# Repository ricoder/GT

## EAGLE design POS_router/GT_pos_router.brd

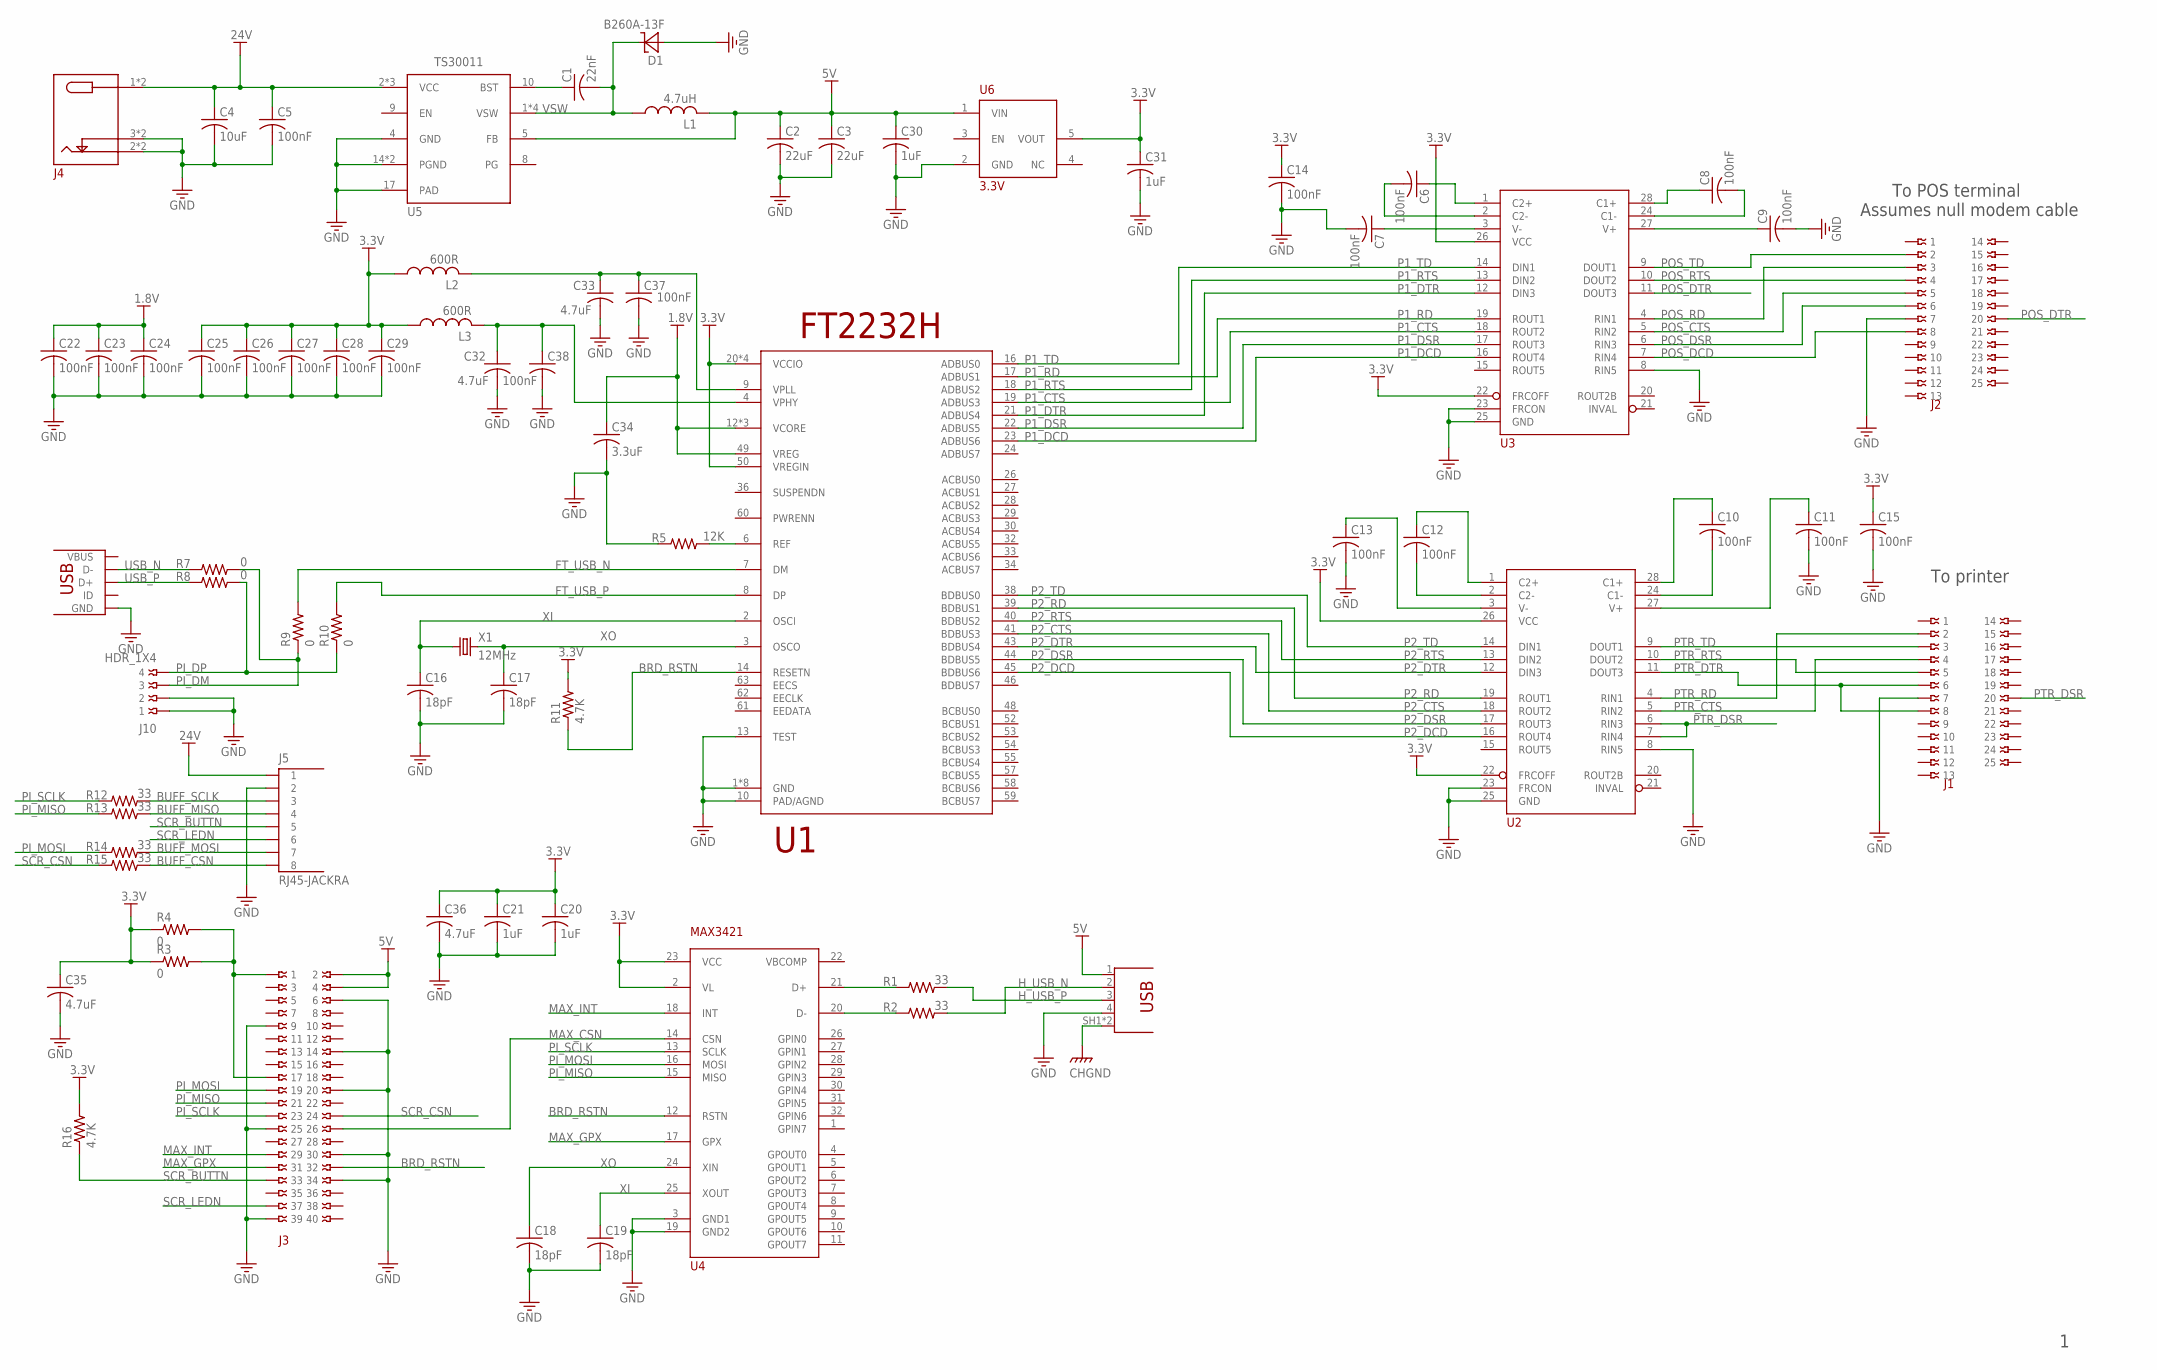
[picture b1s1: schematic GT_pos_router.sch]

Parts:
C1: 22nF; CAPC100X50X55L25N
C2, C3: 22uF; CAPC3216X85L50N
C4: 10uF; CAPC3216X85L50N
C5, C6, C7, C8, C9, C10, C11, C12, C13, C14, C15: 100nF; CAPC1608X87L35N
C16, C17, C18, C19: 18pF; CAPC100X50X55L25N
C20, C21, C30, C31: 1uF; CAPC1608X87L35N
C22, C23, C24, C25, C26, C27, C28, C29, C37, C38: 100nF; CAPC100X50X55L25N
C32, C33, C35, C36: 4.7uF; CAPC2012X140L50N
C34: 3.3uF; CAPC1608X87L35N
D1: B260A-13F; SODFL430X260X240L114X145N
J1: DB25-RA-MALE
J2: DB25-RA-FEMALE
J3: RPI_ZERO_HDR0.2_STACK; RPI_ZERO_HDR
J4: PWR_JACK_SW_NC; PJ-202B
J5: RJ45-JACKRA; RJ45-RA
J8: USB-MICRO-B-SMT-FLG; 10118192-0001LF
J9: USB-A-RECEPT-RA; SS-52100-001
J10: HDR_1X4; HDR_0.1IN_1X4_1MM
L1: 4.7uH; SRN4026
L2, L3: 600R; INDC100X50X55L25N
R1, R2, R12, R13, R14, R15: 33; RESC1005X40L25N
R3, R4, R7, R8, R9, R10: 0; RESC1005X40L25N
R5: 12K; RESC1005X40L25N
R11, R16: 4.7K; RESC1005X40L25N
U1: FT2232H; LQFP64P050_120X120X160N
U2, U3: MAX3243ST-EB; TSSOP28
U4: MAX3421; TQFP32P050_50X50X120N
U5: TS30011; QFN16P05_3X3X10T17X17N
U6: 3.3V; SOT23-5P95_280X160L40X40N
X1: 12MHz; ABLS2

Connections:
1.8V: C22.1, C23.1, C24.1, C34.1, U1.12 (VCORE), U1.37 (VCORE), U1.49 (VREG), U1.64 (VCORE)
3.3V: C14.1, C15.1, C20.1, C21.1, C25.1, C26.1, C27.1, C28.1, C29.1, C31.1, C35.1, C36.1, L2.1, L3.1, R3.1, R4.1, R11.2, R16.2, U1.20 (VCCIO), U1.31 (VCCIO), U1.42 (VCCIO), U1.50 (VREGIN), U1.56 (VCCIO), U2.22 (FRCOFF), U2.26 (VCC), U3.22 (FRCOFF), U3.26 (VCC), U4.2 (VL), U4.23 (VCC), U6.5 (VOUT)
5V: C2.1, C3.1, C30.1, J3.2, J3.4, J9.1 (VBUS), L1.2, U5.5 (FB), U6.1 (VIN)
24V: C4.1, C5.1, J4.1, J4.4 (1), J5.1, U5.2 (VCC), U5.3 (VCC), U5.11 (VCC)
BRD_RSTN: J3.32, R11.1, U1.14 (RESETN), U4.12 (RSTN)
BUFF_CSN: J5.8, R15.2
BUFF_MISO: J5.4, R13.2
BUFF_MOSI: J5.7, R14.2
BUFF_SCLK: J5.3, R12.2
CHGND: J9.SH1 (SHELL), J9.SH2 (SHELL)
FT_USB_N: R9.2, U1.7 (DM)
FT_USB_P: R10.2, U1.8 (DP)
GND: C2.2, C3.2, C4.2, C5.2, C7.2, C9.2, C11.2, C13.2, C14.2, C15.2, C16.2, C17.2, C18.2, C19.2, C20.2, C21.2, C22.2, C23.2, C24.2, C25.2, C26.2, C27.2, C28.2, C29.2, C30.2, C31.2, C32.2, C33.2, C34.2, C35.2, C36.2, C37.2, C38.2, D1.A, J1.7, J2.7, J3.6, J3.9, J3.14, J3.20, J3.25, J3.30, J3.34, J3.39, J4.2, J4.3, J4.5 (2), J4.6 (3), J5.2, J8.5 (GND), J9.4 (GND), J10.1, J10.2, R5.1, U1.1 (GND), U1.5 (GND), U1.10 (PAD/AGND), U1.11 (GND), U1.13 (TEST), U1.15 (GND), U1.25 (GND), U1.35 (GND), U1.47 (GND), U1.51 (GND), U2.8 (RIN5), U2.23 (FRCON), U2.25 (GND), U3.8 (RIN5), U3.23 (FRCON), U3.25 (GND), U4.3 (GND1), U4.19 (GND2), U5.4 (GND), U5.14 (PGND), U5.15 (PGND), U5.17 (PAD), U6.2 (GND)
H_USB_N: J9.2 (D-), R2.2
H_USB_P: J9.3 (D+), R1.2
MAX_CSN: J3.26, U4.14 (CSN)
MAX_GPX: J3.31, U4.17 (GPX)
MAX_INT: J3.29, U4.18 (INT)
unnamed: R1.1, U4.21 (D+)
unnamed: R2.1, U4.20 (D-)
unnamed: C1.1, U5.10 (BST)
unnamed: C6.1, U3.1 (C2+)
unnamed: C6.2, U3.2 (C2-)
unnamed: C7.1, U3.3 (V-)
unnamed: C33.1, C37.1, L2.2, U1.9 (VPLL)
unnamed: C8.1, U3.28 (C1+)
unnamed: C8.2, U3.24 (C1-)
unnamed: C9.1, U3.27 (V+)
unnamed: C32.1, C38.1, L3.2, U1.4 (VPHY)
unnamed: R5.2, U1.6 (REF)
unnamed: C13.1, U2.3 (V-)
unnamed: C12.2, U2.2 (C2-)
unnamed: C12.1, U2.1 (C2+)
unnamed: C10.1, U2.28 (C1+)
unnamed: C10.2, U2.24 (C1-)
unnamed: C11.1, U2.27 (V+)
unnamed: J3.1, J3.17, R3.2, R4.2
P1_CTS: U1.19 (ADBUS3), U3.18 (ROUT2)
P1_DCD: U1.23 (ADBUS6), U3.16 (ROUT4)
P1_DSR: U1.22 (ADBUS5), U3.17 (ROUT3)
P1_DTR: U1.21 (ADBUS4), U3.12 (DIN3)
P1_RD: U1.17 (ADBUS1), U3.19 (ROUT1)
P1_RTS: U1.18 (ADBUS2), U3.13 (DIN2)
P1_TD: U1.16 (ADBUS0), U3.14 (DIN1)
P2_CTS: U1.41 (BDBUS3), U2.18 (ROUT2)
P2_DCD: U1.45 (BDBUS6), U2.16 (ROUT4)
P2_DSR: U1.44 (BDBUS5), U2.17 (ROUT3)
P2_DTR: U1.43 (BDBUS4), U2.12 (DIN3)
P2_RD: U1.39 (BDBUS1), U2.19 (ROUT1)
P2_RTS: U1.40 (BDBUS2), U2.13 (DIN2)
P2_TD: U1.38 (BDBUS0), U2.14 (DIN1)
PI_DM: J10.3, R7.2, R9.1
PI_DP: J10.4, R8.2, R10.1
PI_MISO: J3.21, R13.1, U4.15 (MISO)
PI_MOSI: J3.19, R14.1, U4.16 (MOSI)
PI_SCLK: J3.23, R12.1, U4.13 (SCLK)
POS_CTS: J2.5, U3.5 (RIN2)
POS_DCD: J2.8, U3.7 (RIN4)
POS_DSR: J2.6, U3.6 (RIN3)
POS_DTR: J2.20, U3.11 (DOUT3)
POS_RD: J2.3, U3.4 (RIN1)
POS_RTS: J2.4, U3.10 (DOUT2)
POS_TD: J2.2, U3.9 (DOUT1)
PTR_CTS: J1.4, U2.5 (RIN2)
PTR_DSR: J1.20, U2.6 (RIN3), U2.7 (RIN4)
PTR_DTR: J1.6, J1.8, U2.11 (DOUT3)
PTR_RD: J1.2, U2.4 (RIN1)
PTR_RTS: J1.5, U2.10 (DOUT2)
PTR_TD: J1.3, U2.9 (DOUT1)
SCR_BUTTN: J3.33, J5.5, R16.1
SCR_CSN: J3.24, R15.1
SCR_LEDN: J3.37, J5.6
USB_N: J8.2 (D-), R7.1
USB_P: J8.3 (D+), R8.1
VBCOMP: U4.22 (VBCOMP)
VSW: C1.2, D1.C, L1.1, U5.1 (VSW), U5.12 (VSW), U5.13 (VSW), U5.16 (VSW)
XI: C16.1, C19.1, U1.2 (OSCI), U4.25 (XOUT), X1.1
XO: C17.1, C18.1, U1.3 (OSCO), U4.24 (XIN), X1.2

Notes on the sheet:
To printer
To POS terminal
Assumes null modem cable

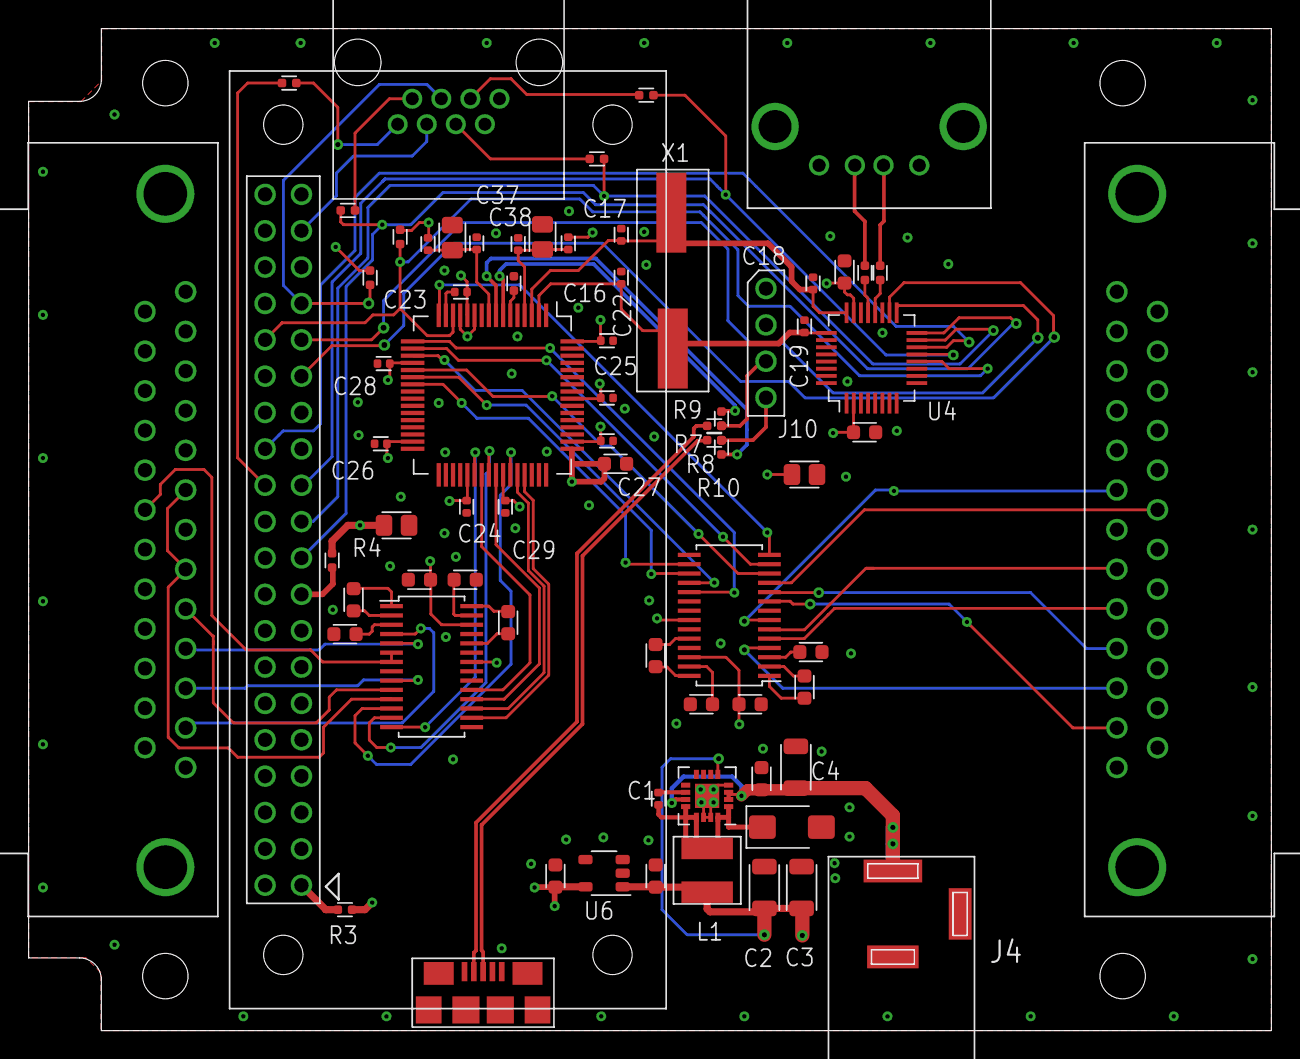
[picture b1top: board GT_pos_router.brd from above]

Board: 4 copper layers, 86.7 x 69.9 mm, 75 parts (0 on the bottom side), 77 nets.

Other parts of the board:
DRILEGEND: DRILEGEND
U$3: FRAME_A_L
U$4: DOCFIELD

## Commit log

2018-07-06 first checkin
2018-07-17 Moved RJ45 to edge and made RA
